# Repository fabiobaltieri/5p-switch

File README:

Five Port Managed Ethernet Switch
=================================

This project is a five port managed switch based on a Micrel KSZ8995M and an
Atmel ATMega168 microcontroller.

License
-------

This program is free software: you can redistribute it and/or modify
it under the terms of the GNU General Public License as published by
the Free Software Foundation, either version 3 of the License, or
(at your option) any later version.

Contents
--------

COPYING     text version of the GPL
README      this file
firmware/   source directory for firmware files
hardware/   source directory for the hardware design files

Firmware
--------

Building requires an avr-gcc toolchain, in the firmware/ directory, to build
run:

  make

Flashing the firmware on the device requires avrdude and a compatible hardware
programmer. Default configuration is stored at the beginning of the Makefile.
To program with the default configuration, run:

  make load

Fuses can be configured running:

  make fuse 

Hardware
--------

All hardware files (schematic, layout and libraries) are in CadSoft Eagle
format.

The switch can be configured in unmanaged mode by not shorting any jumper.

To configure the switch in SPI slave mode, PS[1:0] have to be set to 10, so
just short the pins 1 and 2 of SJ2.

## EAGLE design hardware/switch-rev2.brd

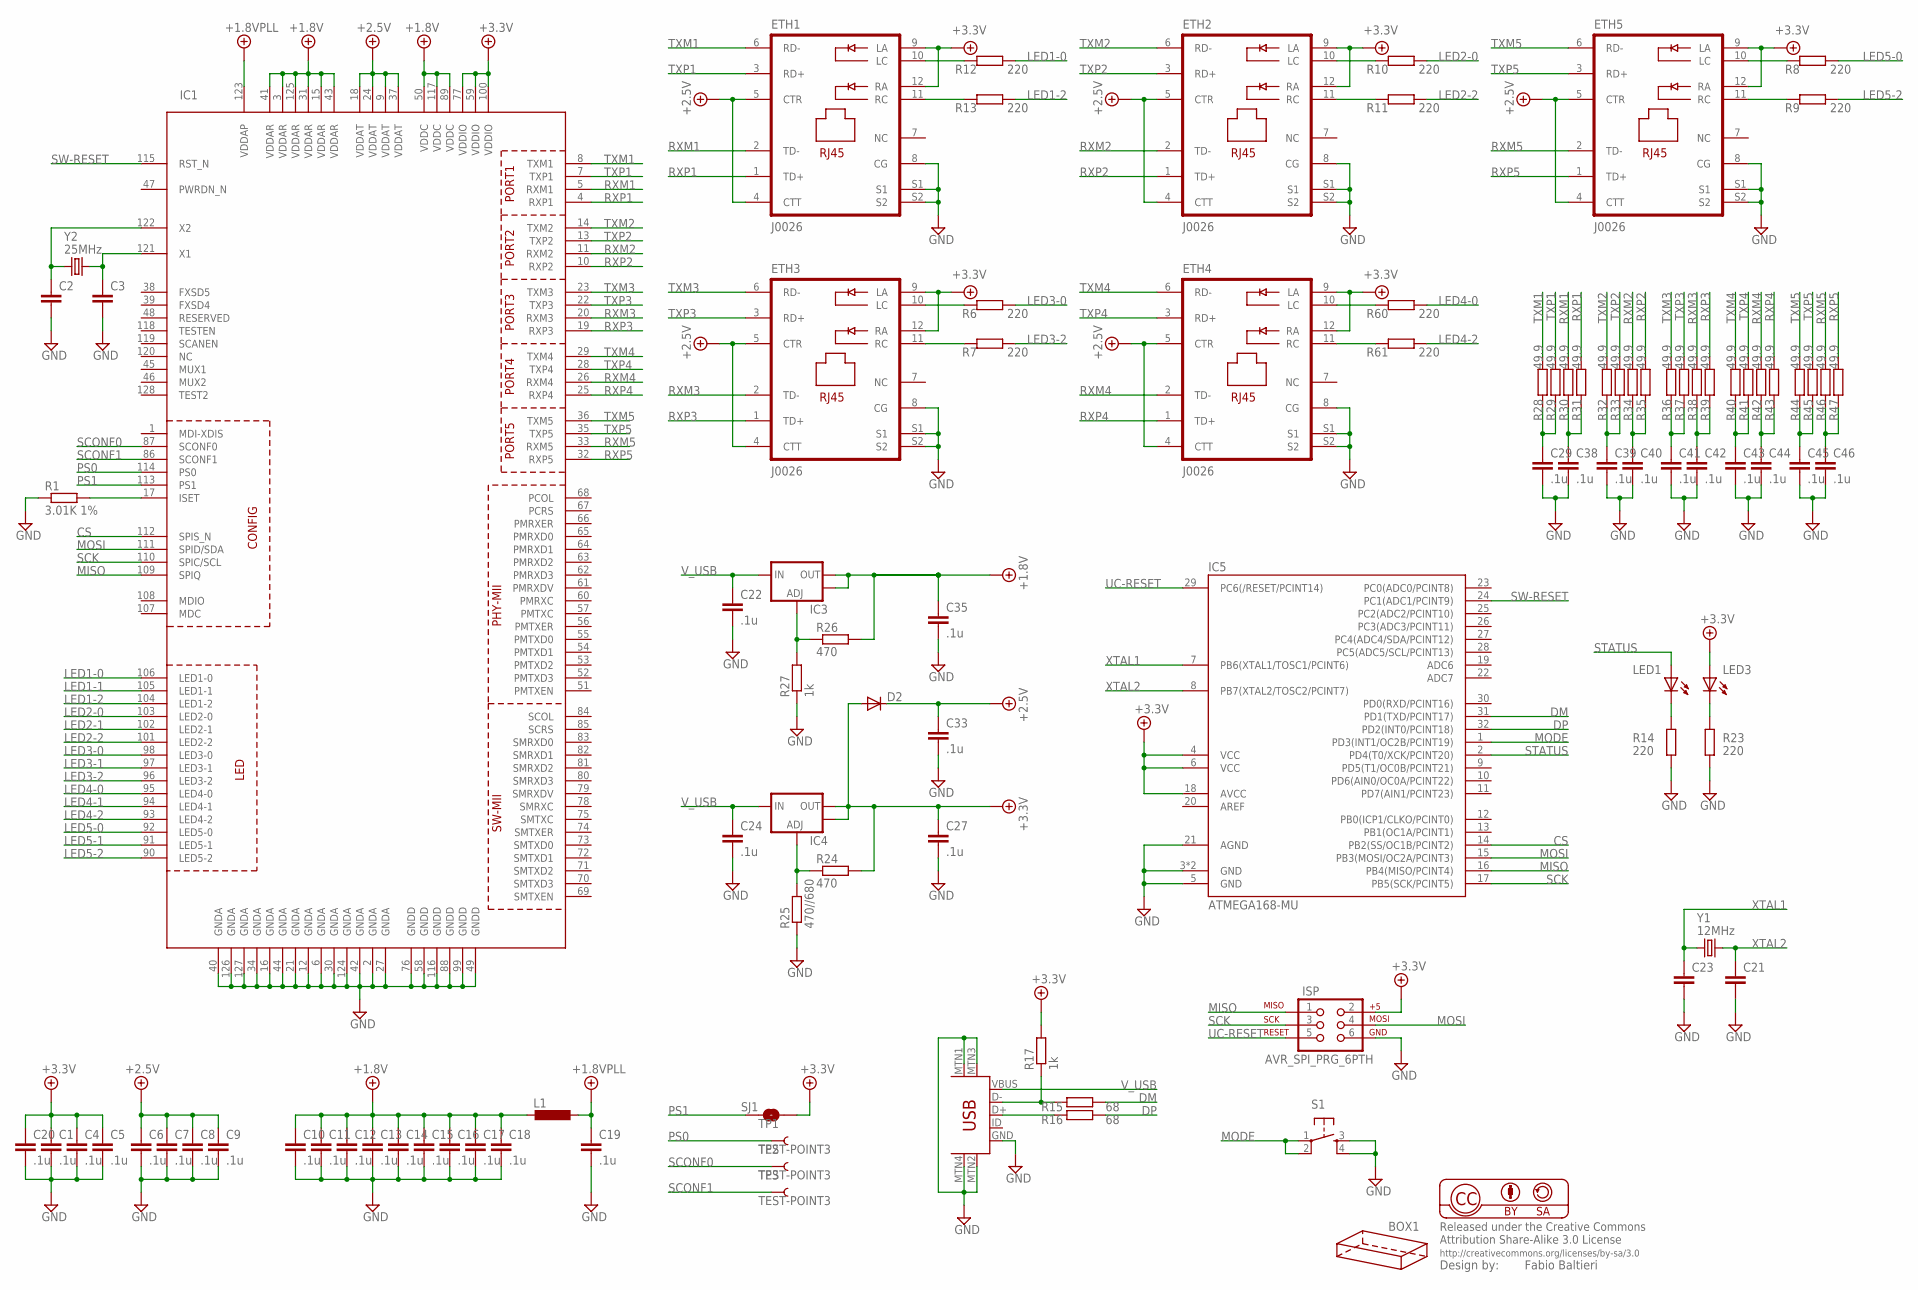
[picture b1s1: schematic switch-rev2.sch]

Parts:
BOX1: HAMMOND-BOX-XXA; 1591XXA
C1, C4, C5, C6, C7, C8, C9, C10, C11, C12, C13, C14, C15, C16, C17, C18, C19, C20, C22, C24, C27, C29, C33, C35, C38, C39, C40, C41, C42, C43, C44, C45, C46: .1u; C0805
C2, C3, C21, C23: C-EUC0805; C0805
D2: DIODE-SMB; SMB
ETH1, ETH2, ETH3, ETH4, ETH5: J0026; PJ-J0
IC1: KS8995MA; PQFP128L
IC3, IC4: V_REG_LM1117SOT223; SOT223
IC5: ATMEGA168-MU; MLF32-TH
ISP: AVR_SPI_PRG_6PTH; 2X3
L1: L-EUL2012C; L2012C
LED1, LED3: LEDCHIPLED_0603; CHIPLED_0603
R1: 3.01K 1%; R0603
R6, R7, R8, R9, R10, R11, R12, R13, R14, R23, R60, R61: 220; R0603
R15, R16: 68; R0603
R17, R27: 1k; R0603
R24, R26: 470; R0603
R25: 470//680; R0603
R28, R29, R30, R31, R32, R33, R34, R35, R36, R37, R38, R39, R40, R41, R42, R43, R44, R45, R46, R47: 49.9; R0603
S1: TAC_SWITCHSMD; TACTILE_SWITCH_SMD
SJ1: SOLDERJUMPERTRACE; SJ_2S-TRACE
TP1, TP2, TP3: TEST-POINT3; PAD.03X.03
U$1: USB-MINIB-5PIN; USB-MINIB
Y1: 12MHz; CRYSTAL-SMD-5X3
Y2: 25MHz; CRYSTAL-SMD-5X3

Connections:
+5V: C1.1, C4.1, C5.1, C20.1, C27.1, D2.A, ETH1.9 (LA), ETH1.12 (RA), ETH2.9 (LA), ETH2.12 (RA), ETH3.9 (LA), ETH3.12 (RA), ETH4.9 (LA), ETH4.12 (RA), ETH5.9 (LA), ETH5.12 (RA), IC1.59 (VDDIO), IC1.77 (VDDIO), IC1.100 (VDDIO), IC4.2 (OUT), IC4.4 (OUT), IC5.4 (VCC), IC5.6 (VCC), IC5.18 (AVCC), ISP.2, LED3.A, R17.2, R24.2, SJ1.2
+5V/1: C6.1, C7.1, C8.1, C9.1, C33.1, D2.C, ETH1.4 (CTT), ETH1.5 (CTR), ETH2.4 (CTT), ETH2.5 (CTR), ETH3.4 (CTT), ETH3.5 (CTR), ETH4.4 (CTT), ETH4.5 (CTR), ETH5.4 (CTT), ETH5.5 (CTR), IC1.9 (VDDAT), IC1.18 (VDDAT), IC1.24 (VDDAT), IC1.37 (VDDAT)
+5V/2: C10.1, C11.1, C12.1, C13.1, C14.1, C15.1, C16.1, C17.1, C18.1, C35.1, IC1.3 (VDDAR), IC1.15 (VDDAR), IC1.31 (VDDAR), IC1.41 (VDDAR), IC1.43 (VDDAR), IC1.50 (VDDC), IC1.89 (VDDC), IC1.117 (VDDC), IC1.125 (VDDAR), IC3.2 (OUT), IC3.4 (OUT), L1.2, R26.2
+5V/4: C19.1, IC1.123 (VDDAP), L1.1
CS: IC1.112 (SPIS_N), IC5.14 (PB2(SS/OC1B/PCINT2))
DM: IC5.31 (PD1(TXD/PCINT17)), R15.1
DP: IC5.32 (PD2(INT0/PCINT18)), R16.1
GND: C1.2, C2.2, C3.2, C4.2, C5.2, C6.2, C7.2, C8.2, C9.2, C10.2, C11.2, C12.2, C13.2, C14.2, C15.2, C16.2, C17.2, C18.2, C19.2, C20.2, C21.2, C22.2, C23.2, C24.2, C27.2, C29.2, C33.2, C35.2, C38.2, C39.2, C40.2, C41.2, C42.2, C43.2, C44.2, C45.2, C46.2, ETH1.8 (CG), ETH1.S1, ETH1.S2, ETH2.8 (CG), ETH2.S1, ETH2.S2, ETH3.8 (CG), ETH3.S1, ETH3.S2, ETH4.8 (CG), ETH4.S1, ETH4.S2, ETH5.8 (CG), ETH5.S1, ETH5.S2, IC1.2 (GNDA), IC1.6 (GNDA), IC1.12 (GNDA), IC1.16 (GNDA), IC1.21 (GNDA), IC1.27 (GNDA), IC1.30 (GNDA), IC1.34 (GNDA), IC1.40 (GNDA), IC1.42 (GNDA), IC1.44 (GNDA), IC1.49 (GNDD), IC1.58 (GNDD), IC1.76 (GNDD), IC1.88 (GNDD), IC1.99 (GNDD), IC1.116 (GNDD), IC1.124 (GNDA), IC1.126 (GNDA), IC1.127 (GNDA), IC5.3 (GND), IC5.5 (GND), IC5.21 (AGND), IC5.TH (GND), ISP.6, R1.1, R14.1, R23.1, R25.1, R27.1, S1.3, S1.4, U$1.GND, U$1.MTN1 (MTN2), U$1.MTN2 (MTN3), U$1.MTN3 (MTN1), U$1.MTN4
LED1-0: IC1.106 (LED1-0), R12.1
LED1-1: IC1.105 (LED1-1)
LED1-2: IC1.104 (LED1-2), R13.1
LED2-0: IC1.103 (LED2-0), R10.1
LED2-1: IC1.102 (LED2-1)
LED2-2: IC1.101 (LED2-2), R11.1
LED3-0: IC1.98 (LED3-0), R6.1
LED3-1: IC1.97 (LED3-1)
LED3-2: IC1.96 (LED3-2), R7.1
LED4-0: IC1.95 (LED4-0), R60.1
LED4-1: IC1.94 (LED4-1)
LED4-2: IC1.93 (LED4-2), R61.1
LED5-0: IC1.92 (LED5-0), R8.1
LED5-1: IC1.91 (LED5-1)
LED5-2: IC1.90 (LED5-2), R9.1
MISO: IC1.109 (SPIQ), IC5.16 (PB4(MISO/PCINT4)), ISP.1
MODE: IC5.1 (PD3(INT1/OC2B/PCINT19)), S1.1, S1.2
MOSI: IC1.111 (SPID/SDA), IC5.15 (PB3(MOSI/OC2A/PCINT3)), ISP.4
unnamed: IC1.17 (ISET), R1.2
unnamed: C2.1, IC1.122 (X2), Y2.1
unnamed: C3.1, IC1.121 (X1), Y2.3 (2)
unnamed: ETH1.11 (RC), R13.2
unnamed: ETH3.10 (LC), R6.2
unnamed: ETH3.11 (RC), R7.2
unnamed: ETH5.10 (LC), R8.2
unnamed: ETH5.11 (RC), R9.2
unnamed: ETH2.10 (LC), R10.2
unnamed: ETH1.10 (LC), R12.2
unnamed: ETH2.11 (RC), R11.2
unnamed: LED1.C, R14.2
unnamed: R15.2, R17.1, U$1.D-
unnamed: R16.2, U$1.D+
unnamed: LED3.C, R23.2
unnamed: IC4.1 (ADJ), R24.1, R25.2
unnamed: IC3.1 (ADJ), R26.1, R27.2
unnamed: C29.1, R28.1, R29.1
unnamed: C38.1, R30.1, R31.1
unnamed: C39.1, R32.1, R33.1
unnamed: C40.1, R34.1, R35.1
unnamed: C41.1, R36.1, R37.1
unnamed: C42.1, R38.1, R39.1
unnamed: C43.1, R40.1, R41.1
unnamed: C44.1, R42.1, R43.1
unnamed: C45.1, R44.1, R45.1
unnamed: C46.1, R46.1, R47.1
unnamed: ETH4.10 (LC), R60.2
unnamed: ETH4.11 (RC), R61.2
PS0: IC1.114 (PS0), TP1.P$1
PS1: IC1.113 (PS1), SJ1.1
RXM1: ETH1.2 (TD-), IC1.5 (RXM1), R30.2
RXM2: ETH2.2 (TD-), IC1.11 (RXM2), R34.2
RXM3: ETH3.2 (TD-), IC1.20 (RXM3), R38.2
RXM4: ETH4.2 (TD-), IC1.26 (RXM4), R42.2
RXM5: ETH5.2 (TD-), IC1.33 (RXM5), R46.2
RXP1: ETH1.1 (TD+), IC1.4 (RXP1), R31.2
RXP2: ETH2.1 (TD+), IC1.10 (RXP2), R35.2
RXP3: ETH3.1 (TD+), IC1.19 (RXP3), R39.2
RXP4: ETH4.1 (TD+), IC1.25 (RXP4), R43.2
RXP5: ETH5.1 (TD+), IC1.32 (RXP5), R47.2
SCK: IC1.110 (SPIC/SCL), IC5.17 (PB5(SCK/PCINT5)), ISP.3
SCONF0: IC1.87 (SCONF0), TP2.P$1
SCONF1: IC1.86 (SCONF1), TP3.P$1
STATUS: IC5.2 (PD4(T0/XCK/PCINT20)), LED1.A
SW-RESET: IC1.115 (RST_N), IC5.24 (PC1(ADC1/PCINT9))
TXM1: ETH1.6 (RD-), IC1.8 (TXM1), R28.2
TXM2: ETH2.6 (RD-), IC1.14 (TXM2), R32.2
TXM3: ETH3.6 (RD-), IC1.23 (TXM3), R36.2
TXM4: ETH4.6 (RD-), IC1.29 (TXM4), R40.2
TXM5: ETH5.6 (RD-), IC1.36 (TXM5), R44.2
TXP1: ETH1.3 (RD+), IC1.7 (TXP1), R29.2
TXP2: ETH2.3 (RD+), IC1.13 (TXP2), R33.2
TXP3: ETH3.3 (RD+), IC1.22 (TXP3), R37.2
TXP4: ETH4.3 (RD+), IC1.28 (TXP4), R41.2
TXP5: ETH5.3 (RD+), IC1.35 (TXP5), R45.2
UC-RESET: IC5.29 (PC6(/RESET/PCINT14)), ISP.5
V_USB: C22.1, C24.1, IC3.3 (IN), IC4.3 (IN), U$1.VBUS
XTAL1: C23.1, IC5.7 (PB6(XTAL1/TOSC1/PCINT6)), Y1.1
XTAL2: C21.1, IC5.8 (PB7(XTAL2/TOSC2/PCINT7)), Y1.3 (2)

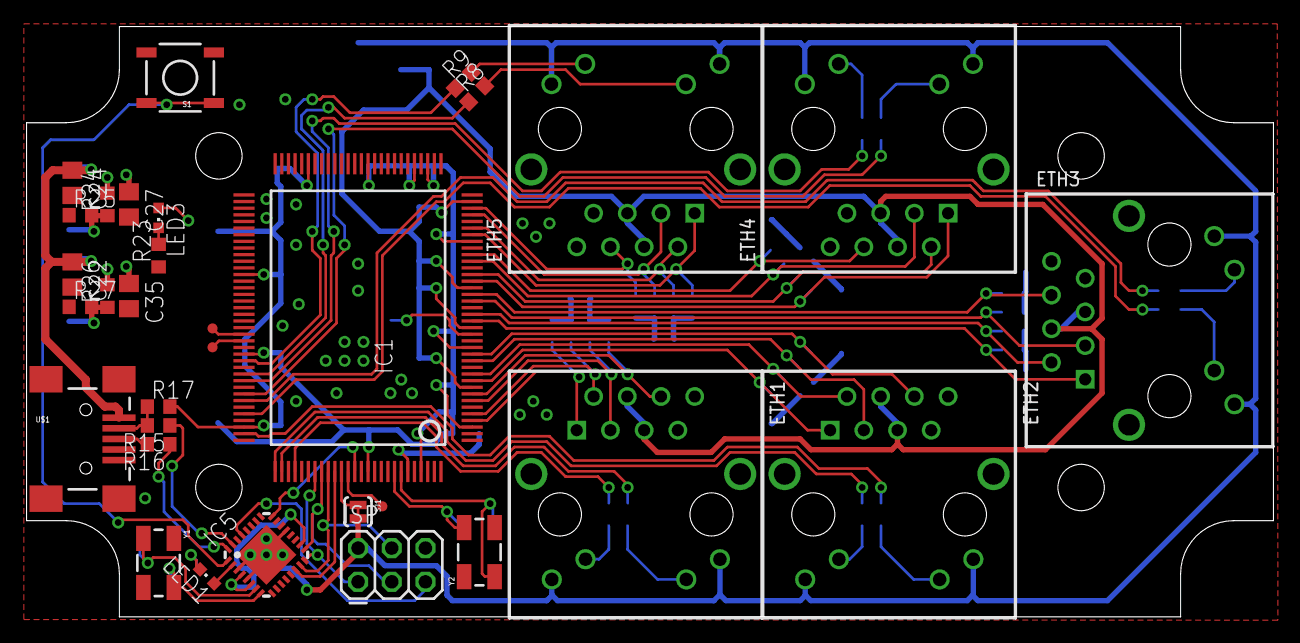
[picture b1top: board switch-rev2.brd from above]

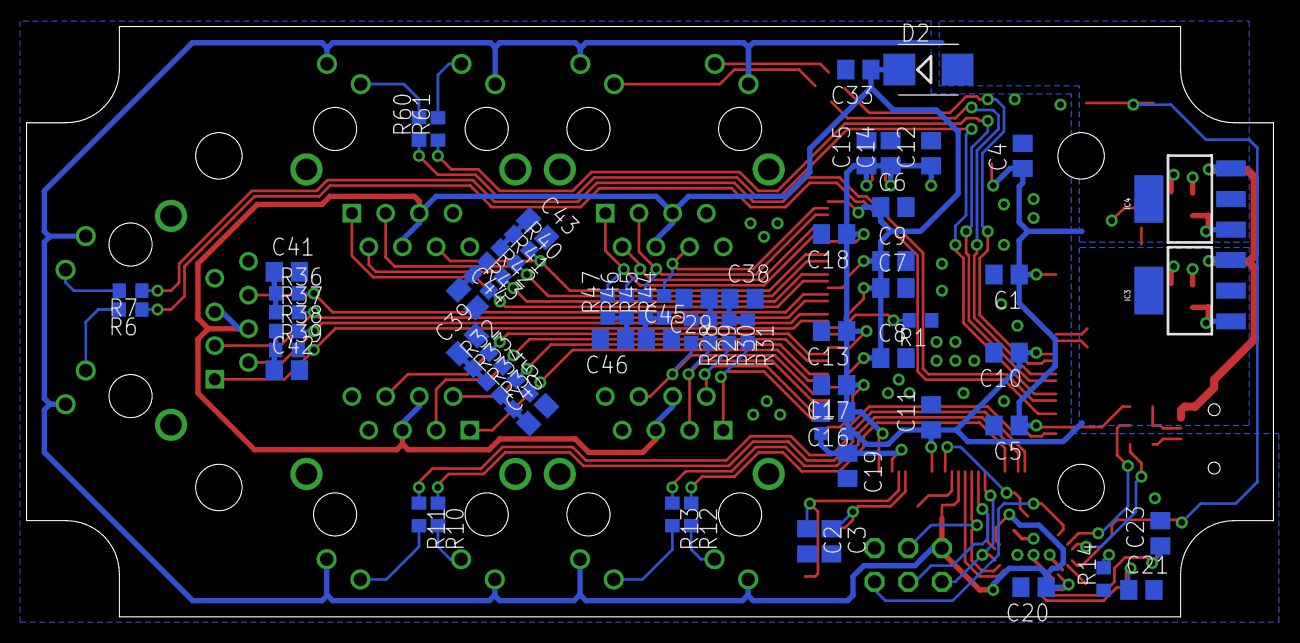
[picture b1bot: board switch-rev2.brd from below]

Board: 2 copper layers, 94.0 x 44.5 mm, 100 parts (67 on the bottom side), 81 nets.

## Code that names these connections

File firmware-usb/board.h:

/* LEDs */

#define LED_A_PORT    PORTD
#define LED_A_DDR     DDRD
#define LED_A         PD6

#define LED_B_PORT    PORTD
#define LED_B_DDR     DDRD
#define LED_B         PD7

#define led_a_on()     LED_A_PORT &= ~_BV(LED_A);
#define led_a_off()    LED_A_PORT |=  _BV(LED_A);
#define led_a_toggle() LED_A_PORT ^=  _BV(LED_A);

#define led_b_on()     LED_B_PORT &= ~_BV(LED_B);
#define led_b_off()    LED_B_PORT |=  _BV(LED_B);
#define led_b_toggle() LED_B_PORT ^=  _BV(LED_B);

#define led_init()				\
	do {					\
		LED_A_DDR |= _BV(LED_A);	\
		LED_B_DDR |= _BV(LED_B);	\
	} while (0);

/* SPI */

#define SPI_DDR  DDRB
#define SPI_PORT PORTB
#define SPI_SCK  PB5
#define SPI_MISO PB4
#define SPI_MOSI PB3
#define SPI_CS   PB2

#define spi_cs_h() SPI_PORT |=  _BV(SPI_CS)
#define spi_cs_l() SPI_PORT &= ~_BV(SPI_CS)

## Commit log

2011-08-18 5p-switch: initial import
2011-08-18 hardware: initial import
2011-08-18 leds.c: removed wrong file insertion
2011-08-18 Makefile: added targets file and fixed include path
2011-08-18 added licence file and headers
2011-08-18 removed compiler warnings
2011-08-18 Makefile: added fuse target
2011-08-18 README: initial not-empty version
2011-08-18 hw: fixed value of cap in reset circuit
2011-08-18 hw: changed microcontroller part number
2011-08-18 README: minor style fixes
2011-08-18 README: added note for pinstrap configuration
2011-08-18 README: changed switch part number
2011-08-19 README added note about hw files format
2011-08-20 added .gitignore file
2011-08-27 Changed README to markdown format
2011-09-05 hardware: added schematic in pdf version
2011-11-20 hardware: add CC BY-SA license
2012-05-15 add firmware-usb
2012-05-15 bootloader: config for 5p-switch
2012-05-15 firmware-usb: fix led config
2012-05-15 add bootloader
2012-05-15 fw-usb: fix usb descriptors
2012-05-15 fw-usb: add led blink hello
2012-05-15 fw-usb: add spi functions
2012-05-15 fw-usb: add ksz8895ma register definitions
2012-05-15 fw-usb: initial start switch
2012-05-15 fw-usb: spi: minor fixes, revers spi_write arguments
2012-05-15 fw-usb: add read reg and write reg usb requests
2012-05-15 fw-usb: generalize port registers
2012-05-15 fw-usb: enable long transfers
2012-05-15 usb-fw: add "get port status" request
2012-05-15 usb-fw: add "get dm table" function
2012-05-15 fw-usb: add "get vlan table" request
2012-05-15 fw-usb: add sw reset to Makefile
2012-05-15 fw-usb: fix dump_dm list
2012-05-15 fw-usb: clean up dump_vlan
2012-05-15 add commandline utility
2012-05-15 usb-fw: fix bug in dump_dm
2012-05-15 usb-fw: add get mib request
2012-05-15 cmdline: remove trailing spaces
2012-05-15 cmdline: add print mib functionality
2012-05-16 cmdline: add dump options
2012-05-16 fw-usb: disable spi 2X mode
    ks8995ma max SPI speed is 5MHz
2012-07-21 hw: add rev2
2012-07-21 hw: move rev2 to the hardware directory
2012-07-21 fw-usb: add missing files
2012-07-23 hw: rev2: progress save
    todo: fix QFN spacing
2012-07-24 hw: rev2: change atmega QFN package
2016-11-30 fw: main: change MODE_A config from 2+2 to 3+1

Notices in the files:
parts and their libraries:
SparkFun-Connectors: Licensing: CC v3.0 Share-Alike You are welcome to use this library for commercial purposes.
balto: Released under the Creative Commons
balto: http://creativecommons.org/licenses/by-sa/3.0
